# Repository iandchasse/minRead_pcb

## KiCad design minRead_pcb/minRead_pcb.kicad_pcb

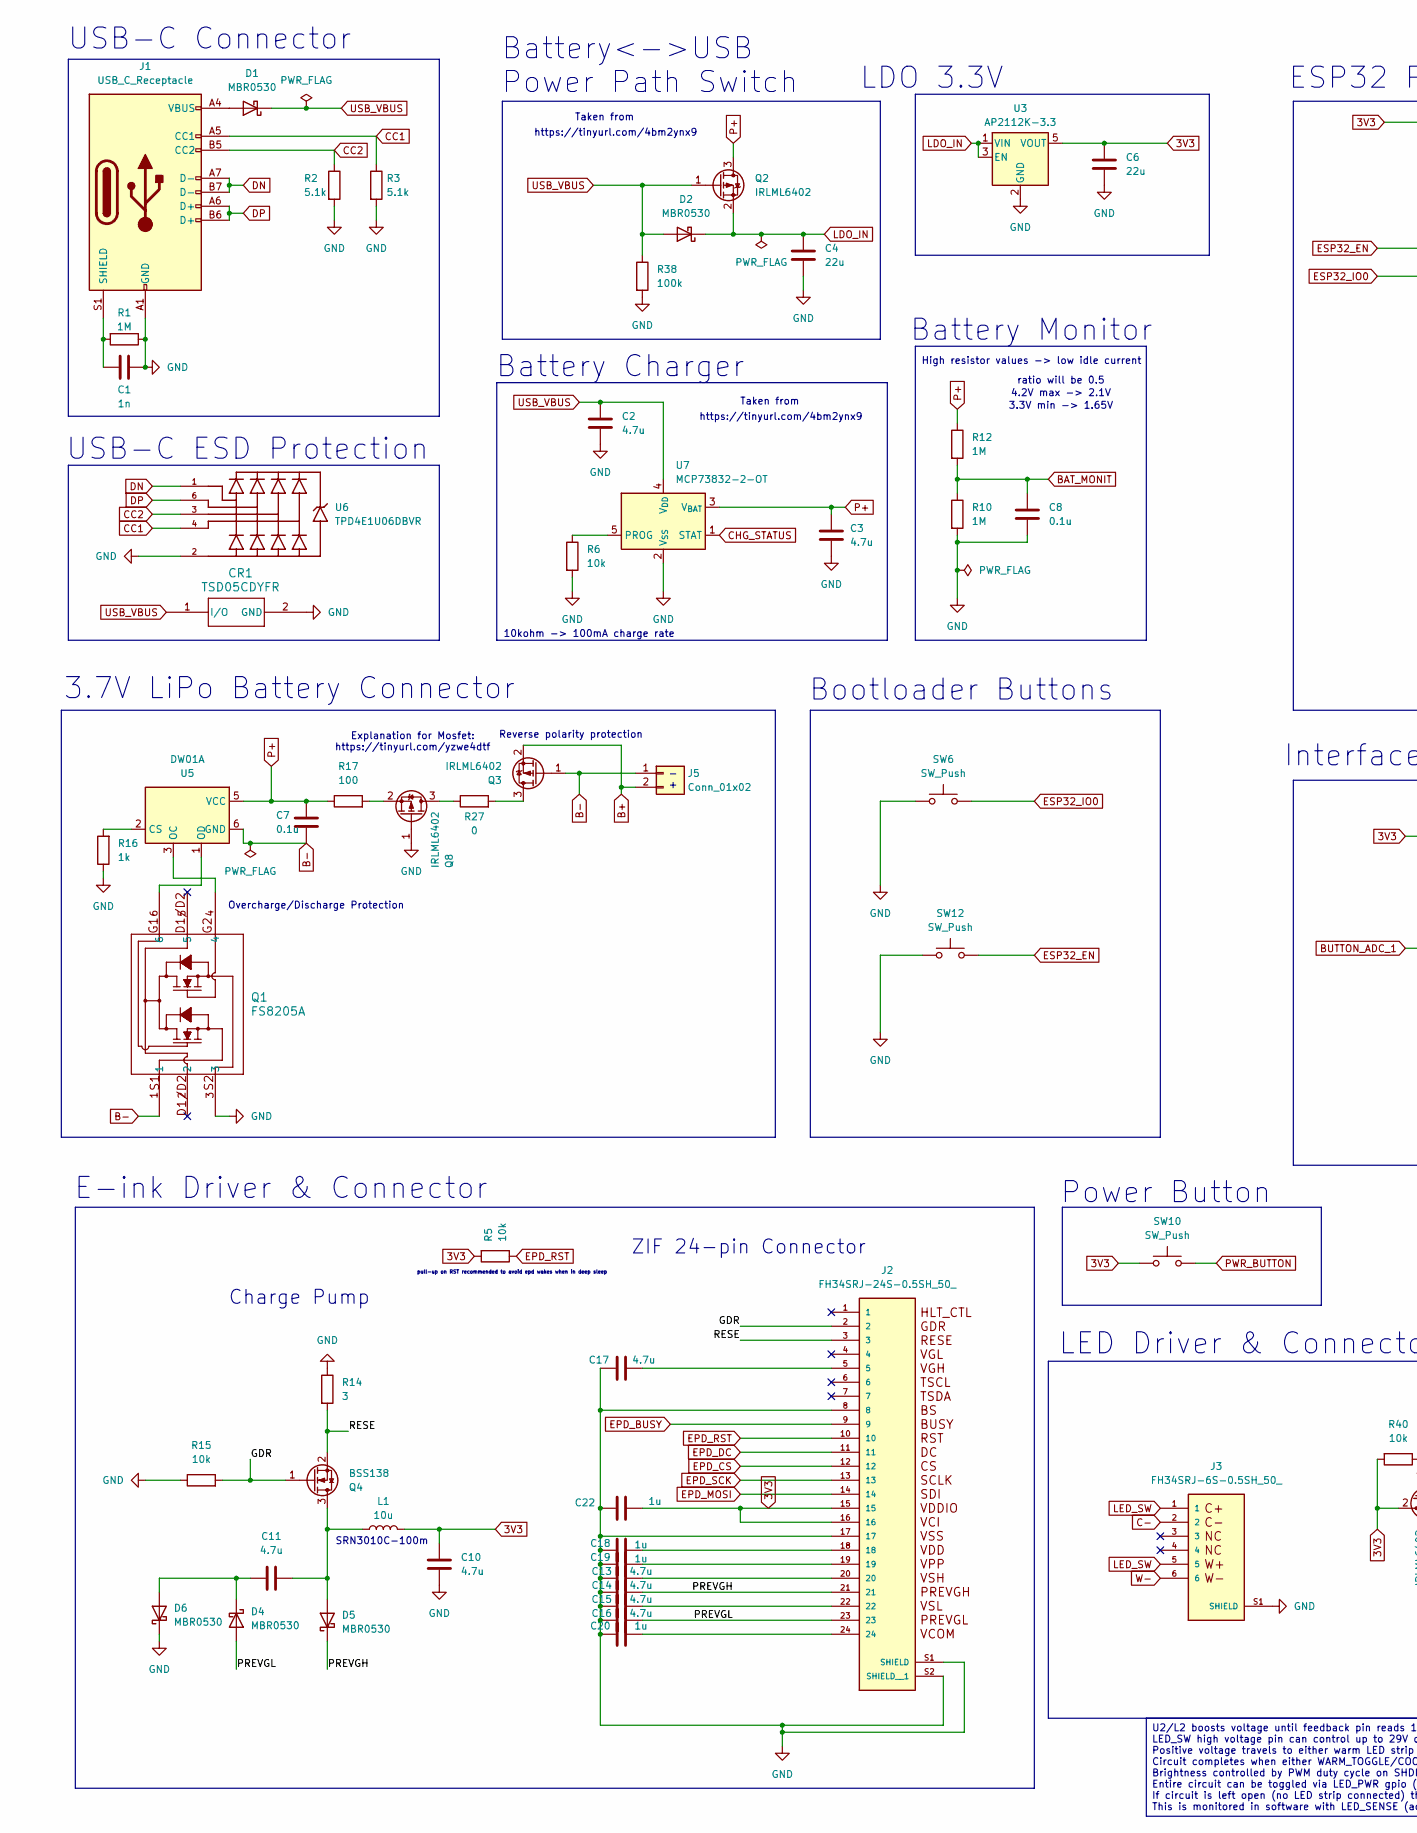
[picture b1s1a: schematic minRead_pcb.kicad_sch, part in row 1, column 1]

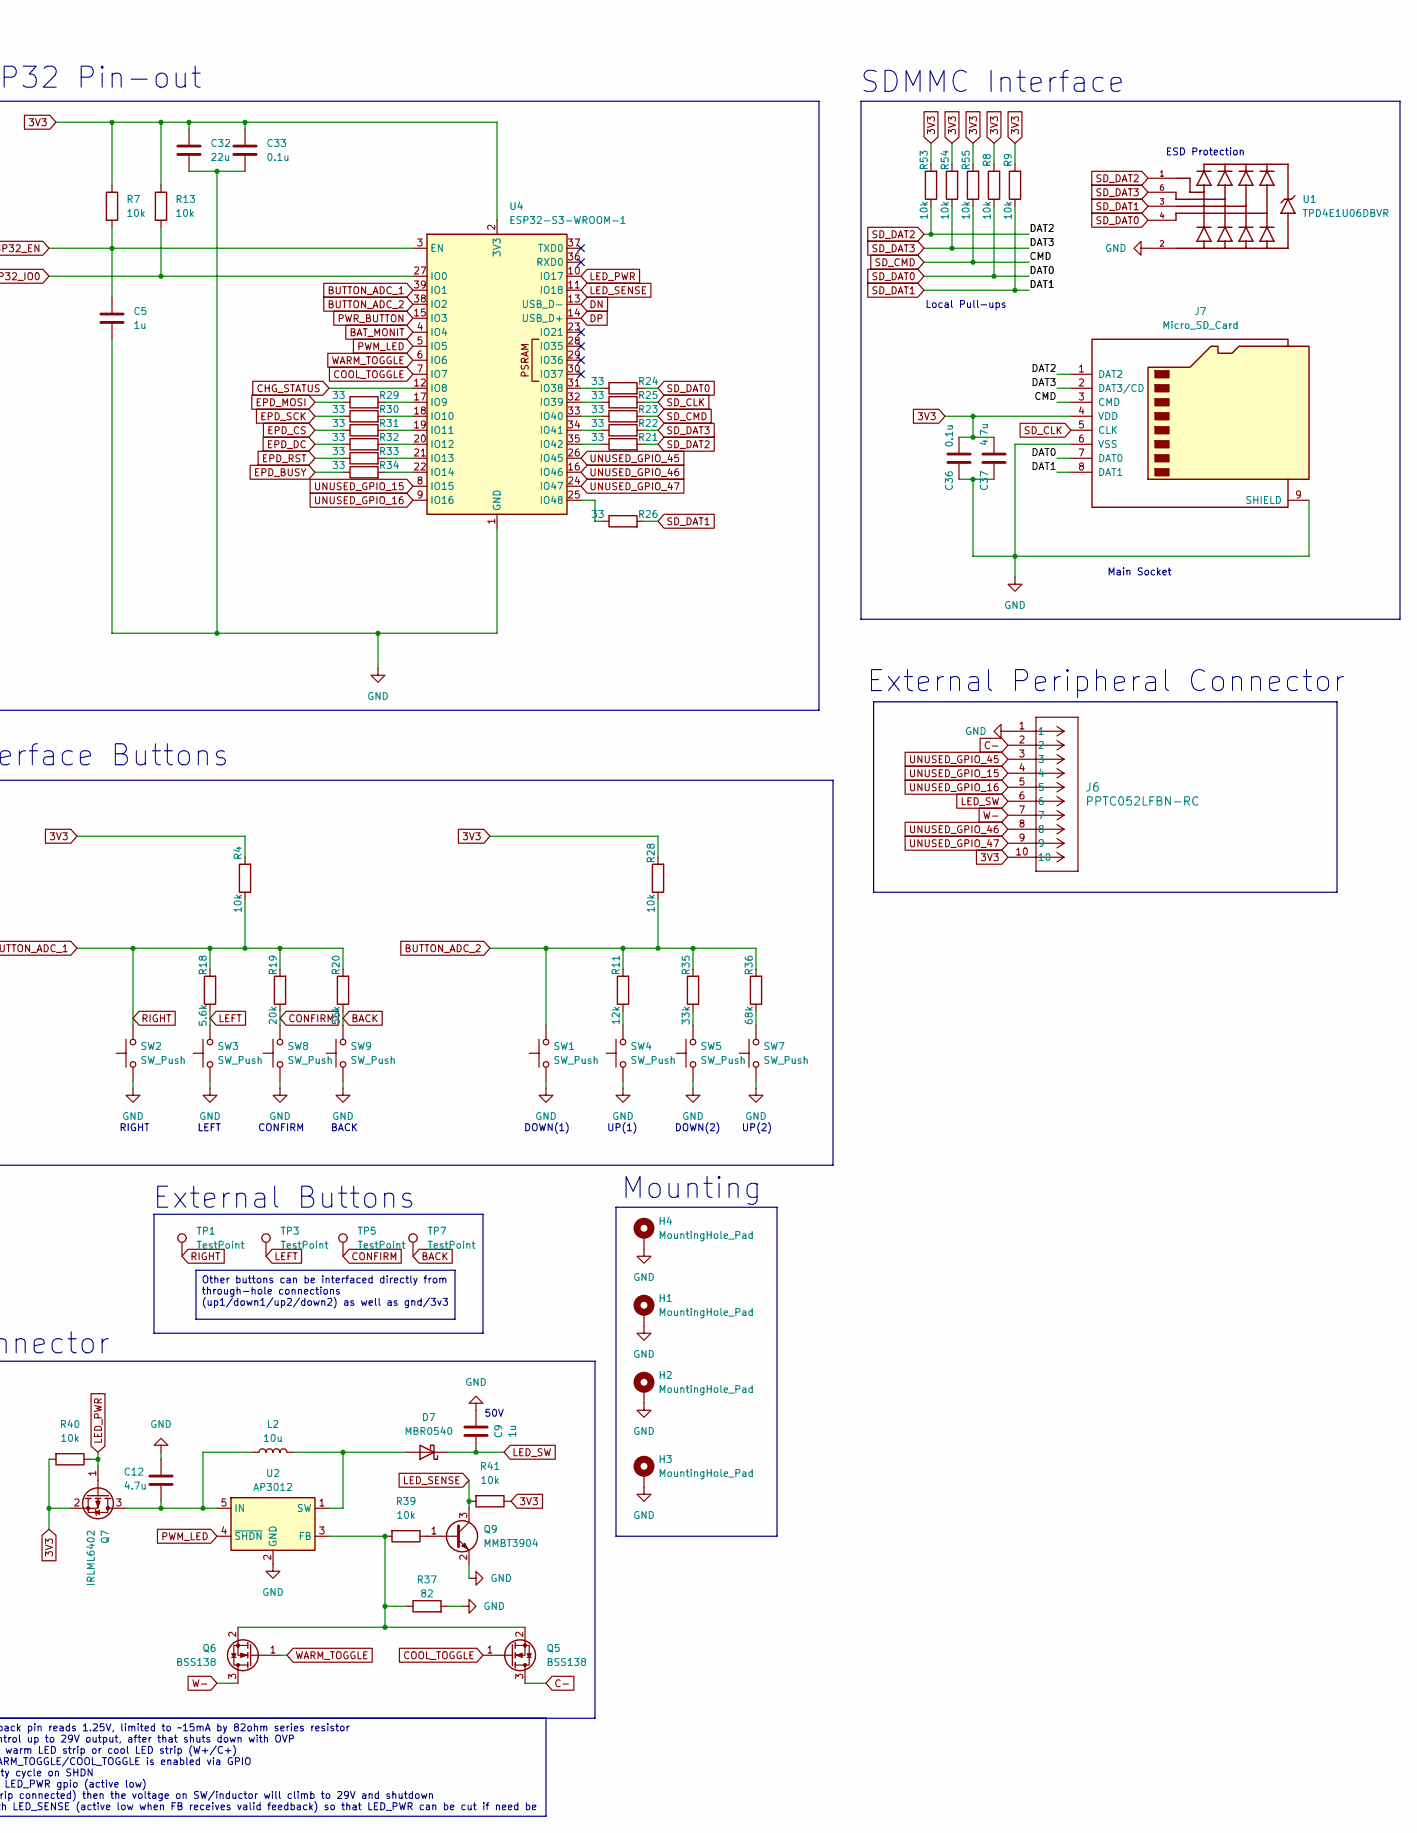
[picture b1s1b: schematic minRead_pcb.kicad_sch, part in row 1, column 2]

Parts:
C1: 1n; C_0805_2012Metric_Pad1.18x1.45mm_HandSolder
C2, C3, C10, C11, C12, C13, C14, C15, C16, C17, C37: 4.7u; C_0805_2012Metric_Pad1.18x1.45mm_HandSolder
C4, C6, C32: 22u; C_0805_2012Metric_Pad1.18x1.45mm_HandSolder
C5, C9, C18, C19, C20, C22: 1u; C_0805_2012Metric_Pad1.18x1.45mm_HandSolder
C7, C8, C33, C36: 0.1u; C_0805_2012Metric_Pad1.18x1.45mm_HandSolder
CR1: TSD05CDYFR; TVS_SOD2_DYF_TEX-M
D1, D2, D4, D5, D6: MBR0530; D_SOD-123
D7: MBR0540; D_SOD-123
H1, H2, H3, H4: MountingHole_Pad; MountingHole_2.2mm_M2_DIN965_Pad_TopBottom
J1: USB_C_Receptacle; USB_C_Receptacle_GCT_USB4085
J2: FH34SRJ-24S-0.5SH_50_; HRS_FH34SRJ-24S-0.5SH_50_
J3: FH34SRJ-6S-0.5SH_50_; HRS_FH34SRJ-6S-0.5SH_50_; DigiKey_Part_Number H125773CT-ND
J5: Conn_01x02; JST_PH_S2B-PH-K_1x02_P2.00mm_Horizontal
J6: PPTC052LFBN-RC; CONN_PPTC052LFBN-RC_SUL
J7: Micro_SD_Card; microSD_HC_Hirose_DM3AT-SF-PEJM5
L1, L2: 10u; IND_SRN3010C-100M
Q1: FS8205A; SOT-23-6_Handsoldering
Q2, Q3, Q7, Q8: IRLML6402; SOT-23_Handsoldering
Q4, Q5, Q6: BSS138; SOT-23
Q9: MMBT3904; SOT-23_Handsoldering
R1, R10, R12: 1M; R_0805_2012Metric_Pad1.20x1.40mm_HandSolder
R2, R3: 5.1k; R_0805_2012Metric_Pad1.20x1.40mm_HandSolder
R4, R5, R6, R7, R8, R9, R13, R15, R28, R39, R40, R41, R53, R54, R55: 10k; R_0805_2012Metric_Pad1.20x1.40mm_HandSolder
R11: 12k; R_0805_2012Metric_Pad1.20x1.40mm_HandSolder
R14: 3; R_0805_2012Metric_Pad1.20x1.40mm_HandSolder
R16: 1k; R_0805_2012Metric_Pad1.20x1.40mm_HandSolder
R17: 100; R_0805_2012Metric_Pad1.20x1.40mm_HandSolder
R18: 5.6k; R_0805_2012Metric_Pad1.20x1.40mm_HandSolder
R19: 20k; R_0805_2012Metric_Pad1.20x1.40mm_HandSolder
R20: 56k; R_0805_2012Metric_Pad1.20x1.40mm_HandSolder
R21, R22, R23, R24, R25, R26, R29, R30, R31, R32, R33, R34: 33; R_0805_2012Metric_Pad1.20x1.40mm_HandSolder
R27: 0; R_0805_2012Metric_Pad1.20x1.40mm_HandSolder
R35: 33k; R_0805_2012Metric_Pad1.20x1.40mm_HandSolder
R36: 68k; R_0805_2012Metric_Pad1.20x1.40mm_HandSolder
R37: 82; R_0805_2012Metric_Pad1.20x1.40mm_HandSolder
R38: 100k; R_0805_2012Metric_Pad1.20x1.40mm_HandSolder
SW1, SW4, SW5, SW7, SW10: SW_Push; SW_Tactile_SPST_Angled_PTS645Vx39-2LFS
SW2, SW3, SW6, SW8, SW9, SW12: SW_Push; SW_SPST_PTS810
TP1, TP3, TP5, TP7: TestPoint; TestPoint_THTPad_1.0x1.0mm_Drill0.5mm
U1, U6: TPD4E1U06DBVR; SOT-23-6_Handsoldering; PARTREV D; DigiKey_Part_Number 296-35965-1-ND
U2: AP3012; SOT-23-5
U3: AP2112K-3.3; SOT-23-5_HandSoldering
U4: ESP32-S3-WROOM-1
U5: DW01A; SOT-23-6_Handsoldering
U7: MCP73832-2-OT; SOT-23-5

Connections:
3V3: C6.1, C10.2, C22.2, C32.1, C33.1, C36.2, C37.2, J2.15, J2.16, J6.10, J7.4 (VDD), L1.2, Q7.2 (S), R4.2, R5.2, R7.1, R8.2, R9.2, R13.1, R28.2, R40.2, R41.1, R53.2, R54.2, R55.2, SW10.1, U3.5 (VOUT), U4.2 (3V3)
/GDR: J2.2, Q4.1 (G), R15.2
/PREVGH: C14.2, D5.1 (K), J2.21
/PREVGL: C16.2, D4.2 (A), J2.23
/RESE: J2.3, Q4.2 (S), R14.2
B+: J5.2, Q3.2 (S)
B-: C7.2, J5.1, Q1.1, Q3.1 (G), U5.6 (GND)
BACK: R20.1, SW9.2, TP7.1
BAT_MONIT: C8.1, R10.1, R12.2, U4.4 (IO4)
BUTTON_ADC_1: R4.1, R18.2, R19.2, R20.2, SW2.2, TP1.1, U4.39 (IO1)
BUTTON_ADC_2: R11.2, R28.1, R35.2, R36.2, SW1.2, U4.38 (IO2)
C-: J3.2, J6.2, Q5.3 (D)
CC1: J1.A5 (CC1), R3.1, U6.4
CC2: J1.B5 (CC2), R2.1, U6.3
CHG_STATUS: U4.12 (IO8), U7.1 (STAT)
CONFIRM: R19.1, SW8.2, TP5.1
COOL_TOGGLE: Q5.1 (G), U4.7 (IO7)
DN: J1.A7 (D-), J1.B7 (D-), U4.13 (USB_D-), U6.1
DP: J1.A6 (D+), J1.B6 (D+), U4.14 (USB_D+), U6.6
EPD_BUSY: J2.9, R34.1
EPD_CS: J2.12, R31.1
EPD_DC: J2.11, R32.1
EPD_MOSI: J2.14, R29.1
EPD_RST: J2.10, R5.1, R33.1
EPD_SCK: J2.13, R30.1
ESP32_EN: C5.1, R7.2, SW12.2, U4.3 (EN)
ESP32_IO0: R13.2, SW6.2, U4.27 (IO0)
GND: C1.1, C2.2, C3.2, C4.2, C5.2, C6.2, C8.2, C9.1, C10.1, C12.1, C13.1, C14.1, C15.1, C16.1, C17.1, C18.1, C19.1, C20.1, C22.1, C32.2, C33.2, C36.1, C37.1, CR1.2 (GND), D6.1 (K), H1.1, H2.1, H3.1, H4.1, J1.A1 (GND), J1.A12 (GND), J1.B1 (GND), J1.B12 (GND), J2.8, J2.17, J2.S1 (SHIELD), J2.S2 (SHIELD__1), J3.S1 (SHIELD), J3.S2 (SHIELD), J6.1, J7.6 (VSS), J7.9 (SHIELD), Q1.3, Q8.1 (G), Q9.2 (E), R1.1, R2.2, R3.2, R6.2, R10.2, R14.1, R15.1, R16.1, R37.2, R38.2, SW1.1, SW2.1, SW3.1, SW4.1, SW5.1, SW6.1, SW7.1, SW8.1, SW9.1, SW12.1, U1.2, U2.2 (GND), U3.2 (GND), U4.1 (GND), U4.40 (GND), U4.41 (GND), U6.2, U7.2 (V_{SS})
LDO_IN: C4.1, D2.1 (K), Q2.2 (S), U3.1 (VIN), U3.3 (EN)
LED_PWR: Q7.1 (G), R40.1, U4.10 (IO17)
LED_SENSE: Q9.3 (C), R41.2, U4.11 (IO18)
LED_SW: C9.2, D7.1 (K), J3.1, J3.5, J6.6
LEFT: R18.1, SW3.2, TP3.1
unnamed: C13.2, J2.20
unnamed: C15.2, J2.22
unnamed: C17.2, J2.5
unnamed: C18.2, J2.18
unnamed: C19.2, J2.19
unnamed: C20.2, J2.24
unnamed: D1.2 (A), J1.A4 (VBUS), J1.A9 (VBUS), J1.B4 (VBUS), J1.B9 (VBUS)
unnamed: C11.1, D4.1 (K), D6.2 (A)
unnamed: C11.2, D5.2 (A), L1.1, Q4.3 (D)
unnamed: D7.2 (A), L2.2, U2.1 (SW)
unnamed: C1.2, J1.S1 (SHIELD), R1.2
unnamed: Q3.3 (D), R27.2
unnamed: Q5.2 (S), Q6.2 (S), R37.1, R39.2, U2.3 (FB)
unnamed: C12.2, L2.1, Q7.3 (D), U2.5 (IN)
unnamed: Q8.3 (D), R27.1
unnamed: Q8.2 (S), R17.2
unnamed: Q9.1 (B), R39.1
unnamed: R11.1, SW4.2
unnamed: R35.1, SW5.2
unnamed: R36.1, SW7.2
unnamed: R29.2, U4.17 (IO9)
unnamed: R30.2, U4.18 (IO10)
unnamed: R31.2, U4.19 (IO11)
unnamed: R32.2, U4.20 (IO12)
unnamed: R33.2, U4.21 (IO13)
unnamed: R34.2, U4.22 (IO14)
unnamed: R24.1, U4.31 (IO38)
unnamed: R25.1, U4.32 (IO39)
unnamed: R23.1, U4.33 (IO40)
unnamed: R22.1, U4.34 (IO41)
unnamed: R21.1, U4.35 (IO42)
unnamed: R26.1, U4.25 (IO48)
unnamed: R16.2, U5.2 (CS)
unnamed: Q1.4, U5.3 (OC)
unnamed: Q1.6, U5.1 (OD)
unnamed: R6.1, U7.5 (PROG)
P+: C3.1, C7.1, Q2.3 (D), R12.1, R17.1, U5.5 (VCC), U7.3 (V_{BAT})
PWM_LED: U2.4 (~SHDN), U4.5 (IO5)
PWR_BUTTON: SW10.2, U4.15 (IO3)
SD_CLK: J7.5 (CLK), R25.2
SD_CMD: J7.3 (CMD), R23.2, R55.1
SD_DAT0: J7.7 (DAT0), R8.1, R24.2, U1.4
SD_DAT1: J7.8 (DAT1), R9.1, R26.2, U1.3
SD_DAT2: J7.1 (DAT2), R21.2, R53.1, U1.1
SD_DAT3: J7.2 (DAT3/CD), R22.2, R54.1, U1.6
UNUSED_GPIO_15: J6.4, U4.8 (IO15)
UNUSED_GPIO_16: J6.5, U4.9 (IO16)
UNUSED_GPIO_45: J6.3, U4.26 (IO45)
UNUSED_GPIO_46: J6.8, U4.16 (IO46)
UNUSED_GPIO_47: J6.9, U4.24 (IO47)
USB_VBUS: C2.1, CR1.1 (I/O), D1.1 (K), D2.2 (A), Q2.1 (G), R38.1, U7.4 (V_{DD})
W-: J3.6, J6.7, Q6.3 (D)
WARM_TOGGLE: Q6.1 (G), U4.6 (IO6)

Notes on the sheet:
Overcharge/Discharge Protection
ratio will be 0.5
SDMMC Interface
Battery<->USB Power Path Switch
RIGHT LEFT CONFIRM BACK
3.7V LiPo Battery Connector
Charge Pump
LED Driver & Connector
SRN3010C-100m
Interface Buttons
3.3V min -> 1.65V
- +
Taken from
pull-up on RST recommended to avoid epd wakes when in deep sleep
50V
External Peripheral Connector
E-ink Driver & Connector
ESD Protection
Battery Charger
ESP32 Pin-out
https://tinyurl.com/4bm2ynx9
Reverse polarity protection
4.2V max -> 2.1V
ZIF 24-pin Connector
Local Pull-ups
DOWN(1) UP(1) DOWN(2) UP(2)
LDO 3.3V
Power Button
High resistor values -> low idle current
Battery Monitor
Explanation for Mosfet:
USB-C ESD Protection
USB-C Connector
Bootloader Buttons
External Buttons
Mounting
10kohm -> 100mA charge rate
Main Socket
https://tinyurl.com/yzwe4dtf
Other buttons can be interfaced directly from through-hole connections (up1/down1/up2/down2) as well as gnd/3v3

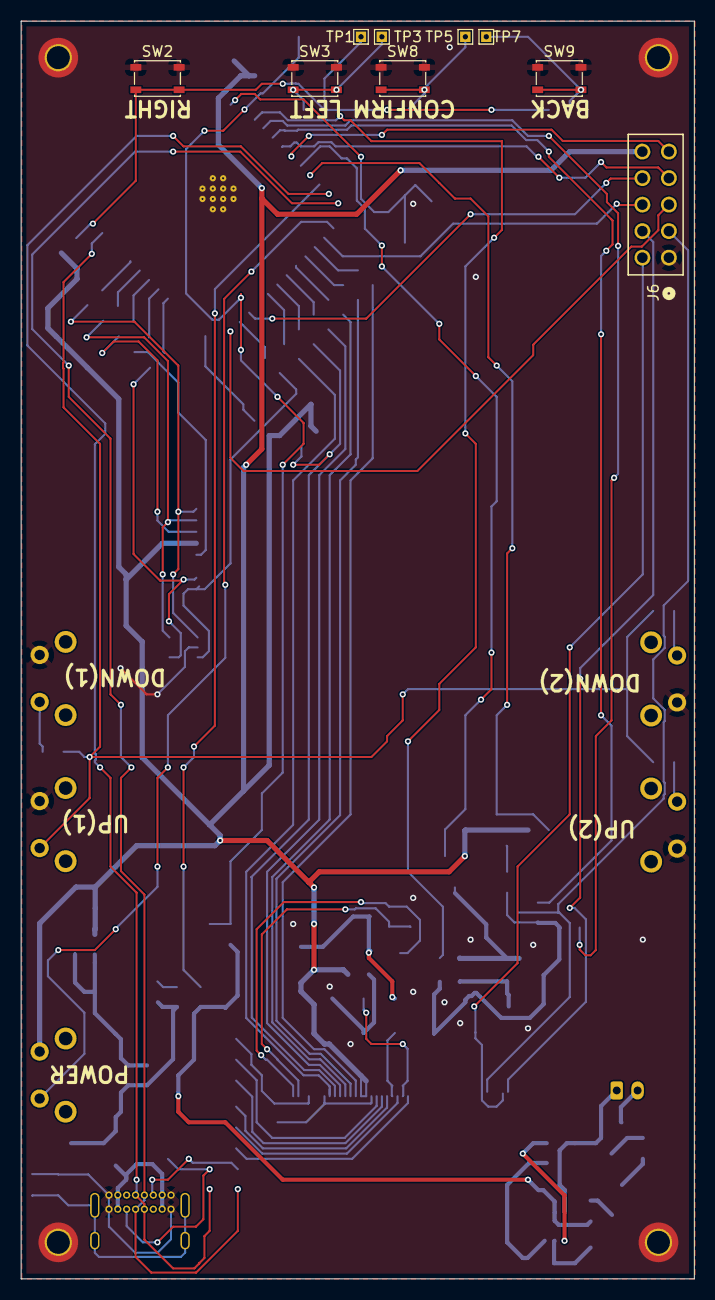
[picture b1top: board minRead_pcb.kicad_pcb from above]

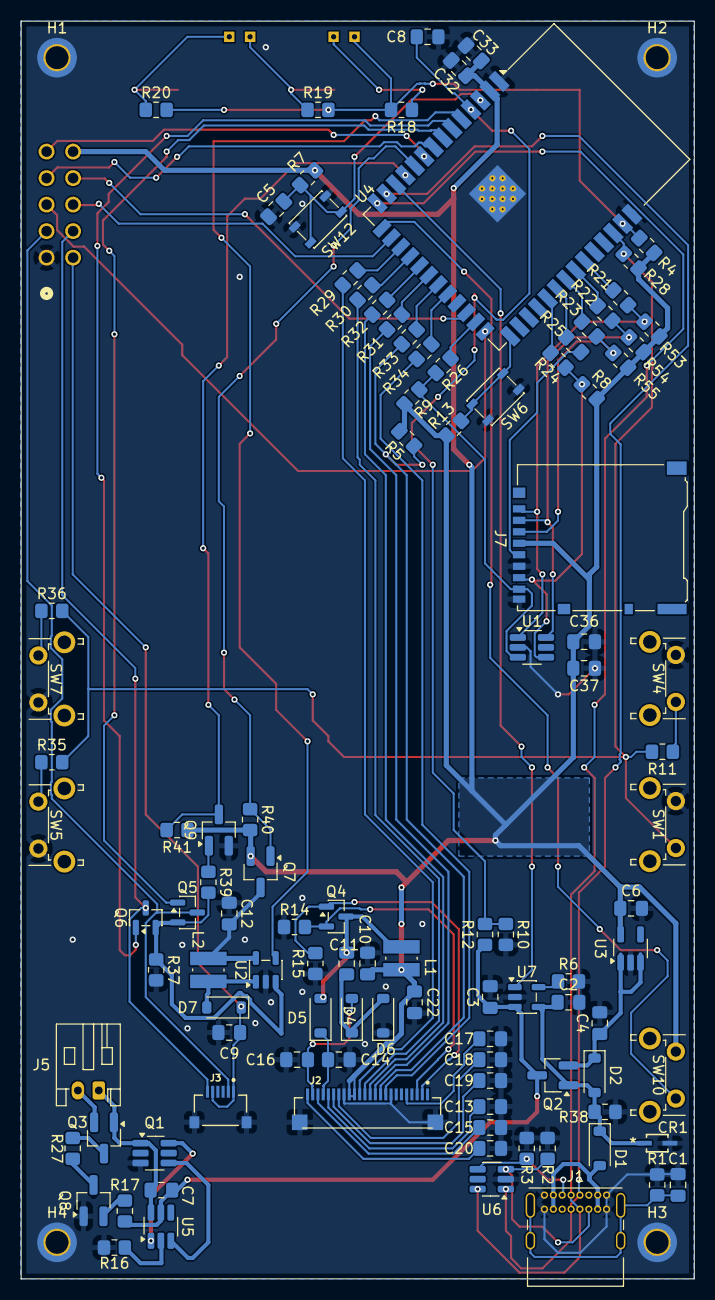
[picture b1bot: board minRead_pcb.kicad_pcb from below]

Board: 2 copper layers, 64.5 x 120.5 mm, 119 parts (110 on the bottom side), 86 nets.

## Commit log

2025-12-13 first pcb revision : shit - needs to revise bq24074 current limit (usb500 mode?) - double check jst battery polarity - need to adjust caps for e-ink driver - double check usb polarity - q4 orientatio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
2025-12-17 - schematic updates: - usb500 mode enabled on bq - charge limit set to 100mA 8.9kohm (safe for small batteries) - series resistors on sd card and epd lines - esd arrays for usb-c and sd-card - increa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
    new layout:
    - adjusted board size
    - very compact
    - need to fill ground planes and check drc errors (a lot because of solder mask)
    - need to adjust jst footprint in case there's a better choice
    - review review review
2025-12-18 draft new rev compact as possible confirmed reverse polarity circuit but need to double check jst connector made sure buttons were as evenly spaced as possible need to ensure every cap is 25v toleran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
2025-12-19 draft1.0
2026-01-14 - fixed diode orientation of eink booster - everything works except eink driver: - rst pin pulls high, dc doesn't toggle, etc etc. - TODO for next rev: - remove reset stabilizer and just route 3v3 to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
2026-01-20 gigantic commit, my bad revised schematic to sanity check turns out my fpc was flipped, now fixed added following schematics: - battery protection circuit - series LED driver - external peripheral co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
    New layout:
    - mostly same as last time, but work done to ensure good grounding for LED/eink circuits
    - eink gpio has minimal crossing/coupl
2026-01-22 updated some things: - confirmed battery protection circuit - added pull up to EPD_RST - changed to 10 pin external IO header instead of 12 pin - reserved gpio 17 and 18 for LED_PWR and LED_SENSE - r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
